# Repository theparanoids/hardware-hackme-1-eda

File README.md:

# ARCHIVED 

# Paranoids Hardware Hackme 1 -- EDA Files
> PCB design files for hackme designed by the Paranoids security team.

The Paranoids security team has designed this PCB to serve as a platform for building CTF (capture-the-flag) challenges.

## Table of Contents

- [Background](#background)
- [Install](#install)
- [Usage](#usage)
- [Contribute](#contribute)
- [License](#license)
- [Shoutouts](#shoutouts)

## Background

PCBs and CTF challenges are fun. Paranoids wanted some fun too. This board was designed by the Paranoids team to be a platform for "hardware" or "embedded systems" capture-the-flag challenges. In a capture-the-flag challenge, a system is designed with deliberate security weaknesses, and the goal for the person playing the challenge is to find and exploit these weaknesses. This board contains a "victim" STM32F4 microcontroller and XC2C32A CPLD. It also has a secondary microcontroller that can act as a debugger for the "victim" microcontroller. This secondary microcontroller can run the open-source [Black Magic Probe](https://github.com/blacksphere/blackmagic) firmware. These components are all conveniently integrated into one board -- no need to connect multiple smaller boards together with a bunch of wires.

## Install

This project is designed in [KiCad](http://kicad-pcb.org/). To edit the files, install a KiCad version at least as recent as 5.0.0-rc2-dev-319-g0ded476.

## Usage

To make changes to the schematic or board layout, open the main `paranoids-hackme-1.pro` project file in KiCad. Schematics for revisions that have gone out to manufacturing are checked in as PDFs for convenience. Gerber files for revisions that have gone out to manufacturing are also checked in for convenience.

This board has been designed with 6 mil trace width, 6 mil minimum spacing, 12 mil minimum drill, and 24 mil minimum via diameter. This is compatible with many PCB manufacturers including [OSHPark](https://oshpark.com/) and [PCBWay](https://www.pcbway.com/).

## Contribute

Please refer to [the contributing.md file](Contributing.md) for information about how to get involved. We welcome issues and questions. Pull Requests may be accepted. However, because manufacturing physical hardware costs money and the Paranoids does not regularly manufacture new batches of PCBs, proposed changes should be thoroughly discussed and agreed upon before submitting a pull request.

## Maintainers
Robert Ou: robert.ou@verizonmedia.com

## License
This project is licensed under the terms of the [MIT](LICENSE-MIT) open source license. Please refer to [LICENSE](LICENSE) for the full terms.

## Shoutouts
* Andrew Zonenberg for his [KiCad libraries](https://github.com/azonenberg/kicad-libraries)
* The [Black Magic Probe](https://github.com/blacksphere/blackmagic) developers for their open-source firmware

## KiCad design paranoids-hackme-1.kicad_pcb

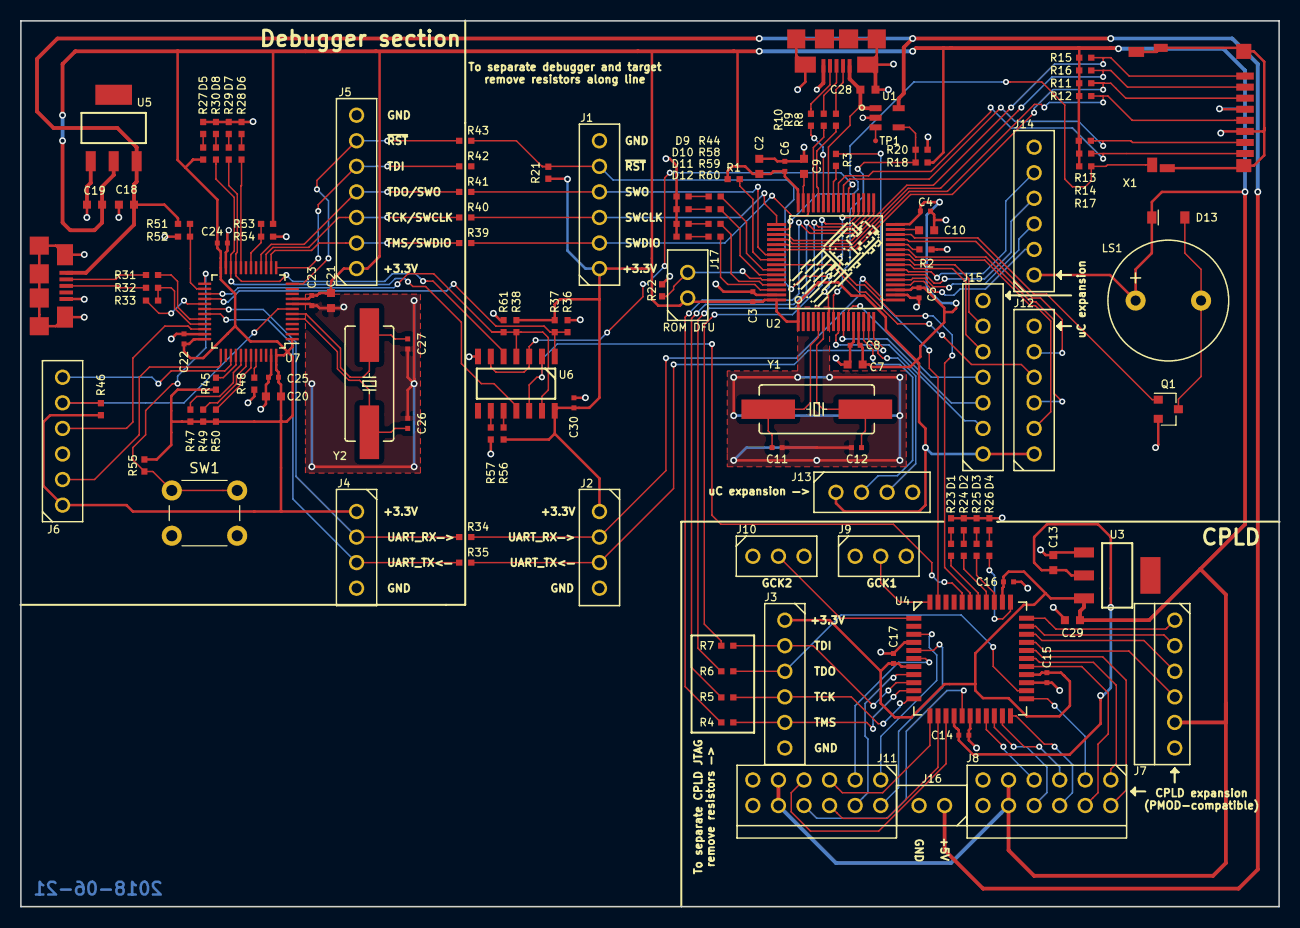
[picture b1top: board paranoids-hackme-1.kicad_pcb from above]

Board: 2 copper layers, 125.0 x 88.0 mm, 136 parts (0 on the bottom side), 138 nets.

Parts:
C2, C13, C18, C19, C20: 4.7uF; EIA_0603_CAP_NOSILK
C3, C4, C5, C6, C8, C14, C15, C16, C17, C22, C23, C24, C25, C30: 0.1uF; EIA_0402_CAP_NOSILK
C7, C21: 1uF; EIA_0603_CAP_NOSILK
C9, C10: 2.2uF; EIA_0603_CAP_NOSILK
C11, C12: 20 pF; EIA_0402_CAP_NOSILK
C26, C27: 20pF; EIA_0402_CAP_NOSILK
C28: 10uF; EIA_0603_CAP_NOSILK
C29: DNP; EIA_0603_CAP_NOSILK
D1, D5, D9: GREEN; EIA_0402_LED
D2, D8, D10: RED; EIA_0402_LED
D3, D7, D11: ORANGE; EIA_0402_LED
D4, D6, D12: YELLOW; EIA_0402_LED
D13: 1N4448; SOD123
J1, J3, J6, J12, J14: Conn_01x06; CONN_HEADER_2.54MM_1x6
J2, J4, J13: Conn_01x04; CONN_HEADER_2.54MM_1x4
J5, J15: Conn_01x07; CONN_HEADER_2.54MM_1x7
J7: Conn_01x06; CONN_HEADER_2.54MM_1x6_RA
J8, J11: Conn_02x06_Top_Bottom; CONN_HEADER_2.54MM_2x6_RA_PMOD_HOST
J9, J10: Conn_01x03; CONN_HEADER_2.54MM_1x3
J16, J17: Conn_01x02; CONN_HEADER_2.54MM_1x2
LS1: CEM-1203; BUZZER_CEM-1203
Q1: 2N7000; SOT-23
R1, R2, R11, R12, R13, R14, R15, R16, R17, R20, R21, R22, R36, R38, R46, R52, R54, R55: 10k; EIA_0402_RES_NOSILK
R3, R4, R5, R6, R7, R10, R34, R35, R39, R40, R41, R42, R43, R45, R48, R49, R56, R57: 0; EIA_0402_RES_NOSILK
R8, R9, R31, R32: 22; EIA_0402_RES_NOSILK
R18, R37, R47, R50, R61: DNP; EIA_0402_RES_NOSILK
R23, R24, R25, R26, R27, R28, R29, R30, R44, R58, R59, R60: 330; EIA_0402_RES_NOSILK
R33: 1.5k; EIA_0402_RES_NOSILK
R51, R53: 4.7k; EIA_0402_RES_NOSILK
Ref**: Val**; NYAN-1CM
SW1: SW_Push_Dual; SW_PUSH_6mm
TP1: Test_Point; TESTPOINT_SMT_0.5MM
U1: STMPS2151STR; STO23-5L
U2: STM32F405Rx; QFP64
U3: LDO1117-1.8V; SOT223-4
U4: XC2C32A-4-VQG44; QFP_44_0.8MM
U5: LDO1117-3.3V; SOT223-4
U6: 74LVC125; SOIC_14_3.9MM
U7: STM32F103Cx; LQFP-48_7x7mm_Pitch0.5mm
USB1, USB2: USB-OTG; USB-MICRO-AB
X1: MicroSD; uSD-114-00841-68
Y1, Y2: 8 MHz; HC49UP

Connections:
+1V8: C13.1, C14.1, U3.2, U4.15
+3V3: C2.1, C3.1, C4.1, C5.1, C6.1, C7.1, C8.1, C15.1, C16.1, C17.1, C19.1, C20.1, C21.1, C22.1, C23.1, C24.1, C25.1, C29.1, C30.1, D13.1, J1.1, J2.1, J3.1, J4.1, J5.1, J6.1, J7.5, J8.5, J8.11, J11.5, J11.11, J12.1, J13.1, J14.1, J15.1, J17.1, LS1.1, R1.1, R11.1, R12.1, R13.1, R14.1, R15.1, R16.1, R17.1, R18.1, R21.1, R27.2, R37.1, R38.1, R45.1, R46.1, R47.1, R49.1, R50.1, R53.1, R55.1, R56.1, U2.1, U2.13, U2.19, U2.32, U2.48, U2.64, U3.3, U4.7, U4.26, U4.35, U5.2, U6.14, U7.1, U7.9, U7.24, U7.36, U7.48, X1.4
+5V: C18.1, J16.1, R51.1, U1.5, U5.3, USB2.1
/debugger/DBG_SWCLK: J6.2, U7.37
/debugger/DBG_SWDIO: J6.4, U7.34
/debugger/DBG_SWO: J6.6, U7.39
/debugger/DBG_nRST: J6.5, R46.2, U7.7
/debugger/LED0: R28.2, U7.20
/debugger/LED1: R29.2, U6.5, U7.21
/debugger/LED2: R30.2, U6.11, U7.22
/debugger/MITM_DBG_EN: R38.2, R61.1, U6.4, U6.13, U7.27
/debugger/MITM_TGT_EN: R36.1, R37.2, U6.1, U7.28
/debugger/MITM_UART_IN: U4.40, U6.2, U6.12
/debugger/TGT_RST: J1.5, R21.2, R43.1, U2.7
/debugger/TGT_RX_FROM_DBG: J2.2, R34.2, U2.17
/debugger/TGT_TDO_TRACESWO: J1.4, R41.1, U2.55
/debugger/TGT_TX_TO_DBG: J2.3, R35.2, U2.16
/target-cpld/CLKIN: R3.2, U4.43
/target-cpld/CPLD_FROM_UC: U2.37, U4.39
/target-uc/AUX_SPI_CLK: J14.3, U2.21
/target-uc/AUX_SPI_CS: J14.2, U2.20
/target-uc/AUX_SPI_MISO: J14.4, U2.22
/target-uc/AUX_SPI_MOSI: J14.5, U2.23
/target-uc/AUX_UART_RX: J13.3, U2.15
/target-uc/AUX_UART_TX: J13.2, U2.14
/target-uc/CPLD_TCK: J3.4, R5.2, U4.11
/target-uc/CPLD_TDI: J3.2, R7.2, U4.9
/target-uc/CPLD_TDO: J3.3, R6.2, U4.24
/target-uc/CPLD_TMS: J3.5, R4.2, U4.10
/target-uc/CPLD_TO_UC: U2.38, U6.3, U6.6
/target-uc/LED0: R44.2, U2.58
/target-uc/LED1: R58.2, U2.59
/target-uc/LED2: R59.2, U2.61
/target-uc/LED3: R60.2, U2.62
/target-uc/SDIO_CD: R17.2, U2.50, X1.CD1
/target-uc/SDIO_CLK: R12.2, U2.53, X1.5
/target-uc/SDIO_CMD: R11.2, U2.54, X1.3
/target-uc/SDIO_D0: R13.2, U2.39, X1.7
/target-uc/SDIO_D1: R14.2, U2.40, X1.8
/target-uc/SDIO_D2: R15.2, U2.51, X1.1
/target-uc/SDIO_D3: R16.2, U2.52, X1.2
/target-uc/SPKR: Q1.1, U2.30
/target-uc/SWCLK: J1.3, R40.1, U2.49
/target-uc/SWDIO: J1.2, R39.1, U2.46
/target-uc/USB_PWR_SW: R18.2, R20.1, U1.4, U2.8
GND: C2.2, C3.2, C4.2, C5.2, C6.2, C7.2, C8.2, C9.2, C10.2, C11.1, C12.1, C13.2, C14.2, C15.2, C16.2, C17.2, C18.2, C19.2, C20.2, C21.2, C22.2, C23.2, C24.2, C25.2, C26.1, C27.2, C28.2, C29.2, C30.2, D1.1, D2.1, D3.1, D4.1, D5.1, D6.1, D7.1, D8.1, D9.1, D10.1, D11.1, D12.1, J1.6, J2.4, J3.6, J4.4, J5.7, J6.3, J7.6, J8.6, J8.12, J9.1, J9.3, J10.1, J10.3, J11.6, J11.12, J12.6, J13.4, J14.6, J15.7, J16.2, Q1.2, R2.1, R20.2, R22.2, R36.2, R48.2, R52.2, R54.2, R57.2, R61.2, SW1.2, U1.2, U2.12, U2.18, U2.63, U3.1, U4.4, U4.17, U4.25, U5.1, U6.7, U7.8, U7.23, U7.35, U7.47, USB1.5, USB1.6, USB1.7, USB1.8, USB1.9, USB1.10, USB1.11, USB2.5, USB2.6, USB2.7, USB2.8, USB2.9, USB2.10, USB2.11, X1.6, X1.CD2, X1.GND1, X1.GND2, X1.GND3, X1.GND4
unnamed: C9.1, U2.47
unnamed: C10.1, U2.31
unnamed: C11.2, U2.5, Y1.1
unnamed: C12.2, U2.6, Y1.2
unnamed: C26.2, U7.5, Y2.1
unnamed: C27.1, U7.6, Y2.2
unnamed: C28.1, U1.1, U2.42, USB1.1
unnamed: D1.2, R23.1
unnamed: D2.2, R24.1
unnamed: D3.2, R25.1
unnamed: D4.2, R26.1
unnamed: D5.2, R27.1
unnamed: D6.2, R28.1
unnamed: D7.2, R29.1
unnamed: D8.2, R30.1
unnamed: D9.2, R44.1
unnamed: D10.2, R58.1
unnamed: D11.2, R59.1
unnamed: D12.2, R60.1
unnamed: D13.2, LS1.2, Q1.3
unnamed: J4.2, R34.1, U7.30
unnamed: J4.3, R35.1, U7.31
unnamed: J5.2, R39.2, U7.14
unnamed: J5.3, R40.2, U7.15
unnamed: J5.4, R41.2, U7.16
unnamed: J5.5, R42.2, U7.13
unnamed: J5.6, R43.2, U7.12
unnamed: J7.1, U4.33
unnamed: J7.2, U4.32
unnamed: J7.3, U4.31
unnamed: J7.4, U4.30
unnamed: J8.1, U4.28
unnamed: J8.2, U4.23
unnamed: J8.3, U4.21
unnamed: J8.4, U4.19
unnamed: J8.7, U4.29
unnamed: J8.8, U4.27
unnamed: J8.9, U4.22
unnamed: J8.10, U4.20
unnamed: J9.2, U4.44
unnamed: J10.2, U4.1
unnamed: J11.1, U4.3
unnamed: J11.2, U4.6
unnamed: J11.3, U4.12
unnamed: J11.4, U4.14
unnamed: J11.7, U4.5
unnamed: J11.8, U4.8
unnamed: J11.9, U4.13
unnamed: J11.10, U4.16
unnamed: J12.2, U2.26
unnamed: J12.3, U2.27
unnamed: J12.4, U2.57
unnamed: J12.5, U2.29
unnamed: J15.2, U2.9
unnamed: J15.3, U2.10
unnamed: J15.4, U2.11
unnamed: J15.5, U2.24
unnamed: J15.6, U2.25
unnamed: J17.2, R22.1, U2.60
unnamed: R1.2, U2.56
unnamed: R2.2, U2.28
unnamed: R3.1, U2.41
unnamed: R4.1, U2.33
unnamed: R5.1, U2.34
unnamed: R6.1, U2.35
unnamed: R7.1, U2.36
unnamed: R8.1, U2.44
unnamed: R8.2, USB1.2
unnamed: R9.1, U2.45
unnamed: R9.2, USB1.3
unnamed: R10.1, U2.43
unnamed: R10.2, USB1.4
unnamed: R23.2, U4.38
unnamed: R24.2, U4.37
unnamed: R25.2, U4.36
unnamed: R26.2, U4.34
unnamed: R31.1, U7.32
unnamed: R31.2, USB2.2
unnamed: R32.1, R33.2, U7.33
unnamed: R32.2, USB2.3
unnamed: R33.1, U7.29
unnamed: R45.2, U7.40
unnamed: R47.2, U7.41
unnamed: R48.1, U7.44
unnamed: R49.2, U7.42
unnamed: R50.2, U7.43
unnamed: R51.2, R52.1, U7.26
unnamed: R53.2, R54.1, U7.18
unnamed: R55.2, SW1.1, U7.25
unnamed: R56.2, U6.10
unnamed: R57.1, U6.9
unnamed: TP1.1, U1.3
